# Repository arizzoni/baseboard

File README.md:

# baseboard
hardware audio effects I/O baseboard

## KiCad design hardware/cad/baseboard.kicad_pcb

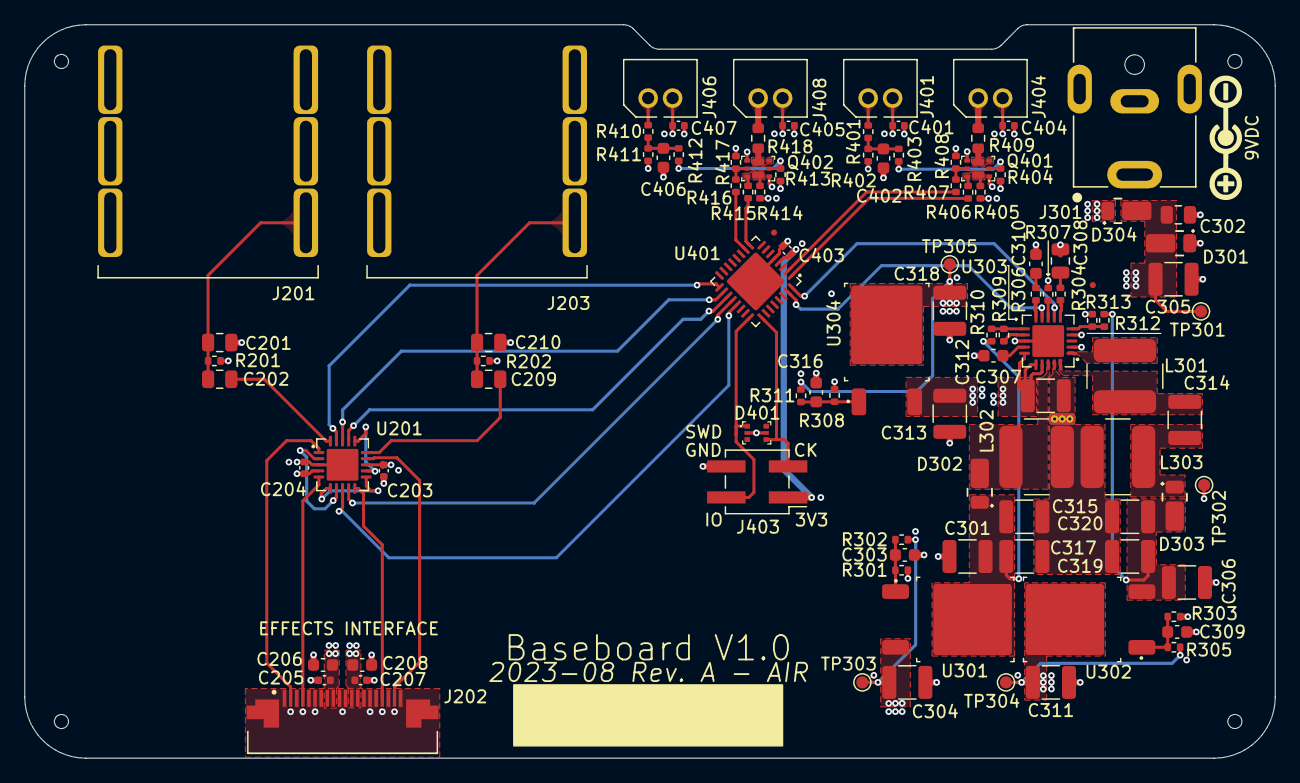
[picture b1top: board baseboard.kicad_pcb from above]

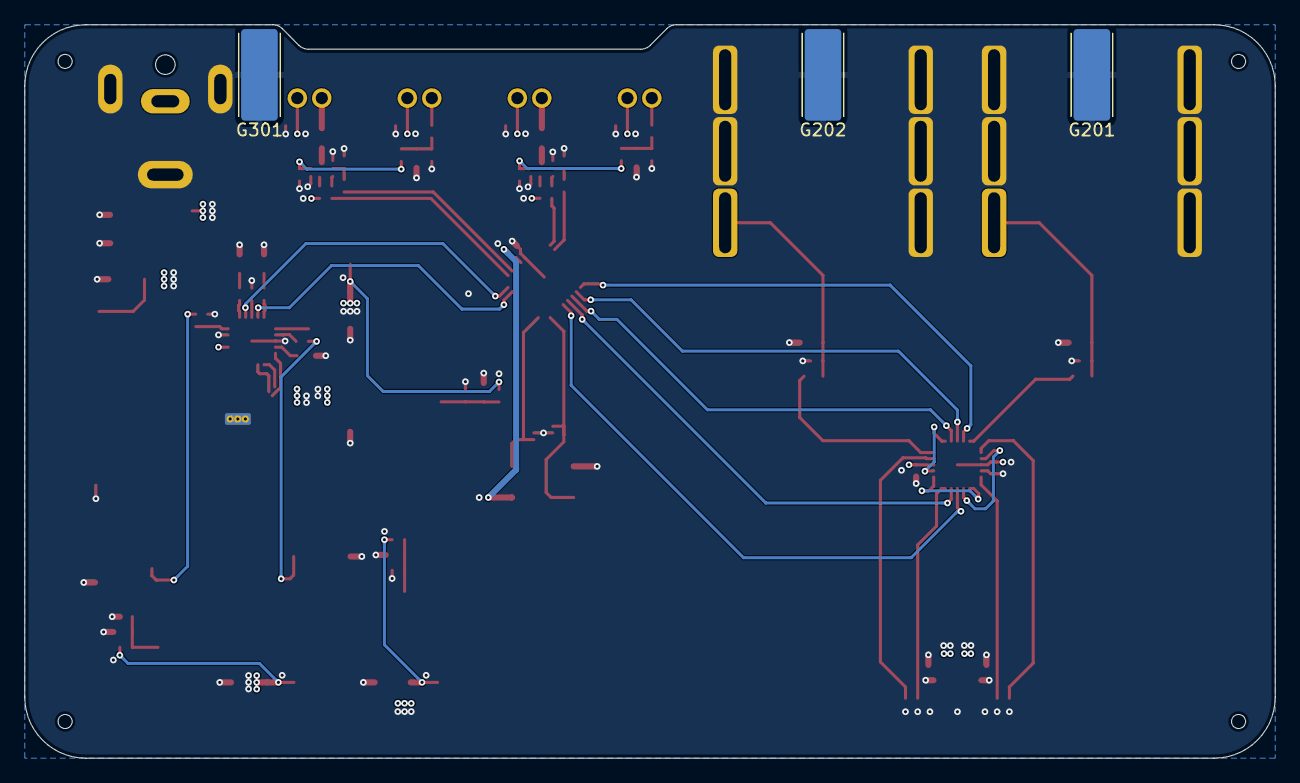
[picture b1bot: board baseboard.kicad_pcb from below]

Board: 4 copper layers, 102.3 x 60.0 mm, 110 parts (3 on the bottom side), 63 nets.

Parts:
C201, C210, C302: 150pF; C_0805_2012Metric
C202, C209: 39nF; C_0805_2012Metric
C203, C204, C205, C207, C401, C403, C404, C405, C407: 100nF; C_0402_1005Metric
C206, C208, C303, C309, C312, C316, C402, C406: 2.2μF; C_0603_1608Metric
C301, C304, C305, C306, C307, C311, C313, C314, C315, C317, C318, C319, C320: 10μF; C_1210_3225Metric
C308: 58nF; C_0805_2012Metric
C310: 10nF; C_0603_1608Metric
D301: DFLZ13Q-7; D_PowerDI-123_THERMAL_PAD
D302, D303, D304: DFLS240L-7; D_PowerDI-123_THERMAL_PAD
D401: RSB12JS2
FID301, FID401: FIDUCIAL; Fiducial_0.5mm_Mask1mm
G201, G202, G301: CHASSIS; Harwin_EMI_Finger_S7061-46R
H401, H402, H403, H404: JLC_TOOLING_HOLE; JLC_Tooling_hole
J201, J203: ACJS-IHS; Amphenol_ACJS-IHS
J202: SFV20R-2STE1HLF; AMPHENOL_SFV20R-2STE1HLF
J301: PJ-063AH; CUI_PJ-063AH
J401, J404, J406, J408: 6-440054-2; TE_HPI_2.0MM_PITCH_MALE_HEADER_2POS
J403: 2x2 PIN HEADER; PinHeader_2x02_P2.54mm_Vertical_SMD
L301, L302, L303: 22μH; L_TDK_VLS6045EX_VLS6045AF
NT301: NET TIE; Net_Tie
Q401, Q402: DMN2050; DMN2050LFDB
R201, R310, R312: 1MΩ; R_0402_1005Metric
R202, R402, R411: 49.9kΩ; R_0402_1005Metric
R301, R303, R404, R408, R413, R417: 750Ω; R_0402_1005Metric
R302, R305, R311, R401, R403, R406, R407, R410, R412, R415, R416: 120Ω; R_0402_1005Metric
R304: 33kΩ; R_0402_1005Metric
R306: 3.3kΩ; R_0402_1005Metric
R307, R313: 71.5kΩ; R_0402_1005Metric
R308, R405, R414: 200Ω; R_0402_1005Metric
R309: 62.5kΩ; R_0402_1005Metric
R409, R418: 15Ω; R_0603_1608Metric
TP301: DC_IN; TestPoint_Pad_D1.0mm
TP302: GND; TestPoint_Pad_D1.0mm
TP303: -9V; TestPoint_Pad_D1.0mm
TP304: +9V; TestPoint_Pad_D1.0mm
TP305: +3V3; TestPoint_Pad_D1.0mm
U201: ADG5434; LFCSP-20-1EP_4x4mm_P0.5mm_EP2.6x2.6mm
U301: LM337KVURG3; TO-252-2
U302, U304: LM317MDT-TR; TO-252-2
U303: ADP5070; LFCSP-20-1EP_4x4mm_P0.5mm_EP2.6x2.6mm
U401: STM32G031K8U6; QFN-32-1EP_5x5mm_P0.5mm_EP3.45x3.45mm

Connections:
+3V3: C318.2, C401.2, C403.2, C404.2, C405.2, C407.2, J401.2, J403.1, J404.2, J406.2, J408.2, R311.1, R405.1, R414.1, TP305.1, U304.2 (VO), U401.4 (VDD)
+9V: C203.1, C205.2, C206.2, C311.2, J202.8, J202.9, R305.1, TP304.1, U201.13 (VDD), U302.2 (VO)
+9V_EN: U303.7 (EN1), U401.32 (PB8)
+12V_RAW: C306.2, C319.2, C320.2, D303.1 (K), R312.2, U302.3 (VI)
-9V: C204.1, C207.2, C208.2, C304.2, J202.12, J202.13, R302.1, TP303.1, U201.3 (VSS), U201.21 (VSS), U301.3 (VO)
-9V_EN: U303.9 (EN2), U401.31 (PB7)
-12V_RAW: C301.2, C315.2, C317.2, D302.2 (A), R310.1, U301.2 (VI)
/AUDIO/AUDIO_A_TO_B: U201.6 (D2), U201.11 (D3)
/AUDIO/AUDIO_IN-: C201.1, C202.2, J201.T, R201.1
/AUDIO/AUDIO_OUT: C209.1, C210.1, J203.T, R202.1
/AUDIO/BYPASS_A: U201.2 (S1B), U201.7 (S2A)
/AUDIO/BYPASS_B: U201.12 (S3B), U201.16 (S4A)
/MICROCONTROLLER/SWDCK: D401.4, J403.3, U401.25 (PA14)
/MICROCONTROLLER/SWDIO: D401.1, J403.2, U401.24 (PA13)
/MICROCONTROLLER/VD_FTSW_A: Q402.6 (D), R414.2, R415.1
/MICROCONTROLLER/VD_FTSW_B: Q401.6 (D), R405.2, R406.1
/MICROCONTROLLER/VG_FTSW_A: Q402.2 (G), R412.2, R413.1
/MICROCONTROLLER/VG_FTSW_B: Q401.2 (G), R403.2, R404.1
/MICROCONTROLLER/VG_LEDA: Q402.5 (G), R416.2, R417.1
/MICROCONTROLLER/VG_LEDB: Q401.5 (G), R407.2, R408.1
/MICROCONTROLLER/VS_A: Q402.3 (D), R418.2
/MICROCONTROLLER/VS_B: Q401.3 (D), R409.2
/MICROCONTROLLER/V_FTSW_FILT_A: C406.2, R410.2, R411.2, R412.1
/MICROCONTROLLER/V_FTSW_FILT_B: C402.2, R401.2, R402.2, R403.1
/MICROCONTROLLER/V_FTSW_RAW_A: J406.1, R410.1
/MICROCONTROLLER/V_FTSW_RAW_B: J401.1, R401.1
/MICROCONTROLLER/V_LEDA: J408.1, R418.1
/MICROCONTROLLER/V_LEDB: J404.1, R409.1
/POWER/3V3REG_FB: C316.2, R308.1, R311.2, U304.1 (ADJ)
/POWER/+9VREG_FBP: C309.2, R303.1, R305.2, U302.1 (ADJ)
/POWER/-9VREG_FBN: C303.2, R301.1, R302.2, U301.1 (ADJ)
/POWER/DC_IN_RAW: D304.2 (A), J301.2
/POWER/VSW1A: C314.2, L301.2, U303.20 (SW1)
/POWER/VSW1B: C314.1, D303.2 (A), L303.2
/POWER/VSW1INBK: L301.1, U303.1 (INBK)
/POWER/VSW2: D302.1 (K), L302.2, U303.18 (SW2)
/POWER/VSW_COMP1: R304.2, U303.6 (COMP1)
/POWER/VSW_COMP2: R306.2, U303.10 (COMP2)
/POWER/VSW_FB1: R312.1, R313.2, U303.5 (FB1)
/POWER/VSW_FB2: R309.1, R310.2, U303.11 (FB2)
/POWER/VSW_SOFT_START: R307.2, U303.8 (SS)
/POWER/VSW_VREF: R309.2, U303.12 (VREF)
/POWER/VSW_VREG: C312.2, U303.14 (VREG)
AUDIO_IN_A: J202.2, U201.1 (D1)
AUDIO_IN_B: J202.17, U201.10 (S3A)
AUDIO_IN_FILT: C202.1, U201.20 (S1A)
AUDIO_OUT_A: J202.4, U201.5 (S2B)
AUDIO_OUT_B: J202.19, U201.14 (S4B)
AUDIO_OUT_FILT: C209.2, U201.15 (D4)
DC_IN: C302.1, C305.2, C307.2, C313.2, D301.1 (K), D304.1 (K), TP301.1, U303.2 (SYNC/FREQ), U303.15 (PVIN1), U303.16 (PVINSYS), U303.17 (PVIN2), U304.3 (VI)
FTSW_A: R415.2, U401.9 (PA2)
FTSW_B: R406.2, U401.1 (PB9)
GND: C201.2, C203.2, C204.2, C205.1, C206.1, C207.1, C208.1, C210.2, C301.1, C302.2, C303.1, C304.1, C305.1, C306.1, C308.1, C309.1, C310.1, C311.1, C312.1, C313.1, C316.1, C318.1, C401.1, C402.1, C403.1, C404.1, C405.1, C406.1, C407.1, D301.2 (A), D401.2, D401.5, G201.1, G202.1, G301.1, J201.R, J201.RN, J201.S, J201.SN, J201.TN, J202.1, J202.3, J202.5, J202.6, J202.7, J202.10, J202.11, J202.14, J202.15, J202.16, J202.18, J202.20, J202.SH1, J202.SH2, J203.R, J203.RN, J203.S, J203.SN, J203.TN, J301.1, J301.S1, J301.S2, J403.4, NT301.2, Q401.1 (S), Q401.4 (S), Q402.1 (S), Q402.4 (S), R201.2, R202.2, R301.2, R303.2, R307.1, R308.2, R313.1, R402.1, R404.2, R408.2, R411.1, R413.2, R417.2, TP302.1, U201.4 (GND), U303.4 (SLEW), U303.13 (AGND), U303.21 (AGND), U401.5 (VSS), U401.33 (VSS)
GND1: C307.1, C315.1, C317.1, C319.1, C320.1, L302.1, L303.1, NT301.1, U303.19 (PGND)
LEDA_EN: R416.1, U401.10 (PA3)
LEDB_EN: R407.1, U401.2 (PC14)
unnamed: C308.2, R304.1
unnamed: C310.2, R306.1
SW_IN1: U201.19 (IN1), U401.17 (PB2)
SW_IN2: U201.8 (IN2), U401.21 (PA10/NC)
SW_IN3: U201.9 (IN3), U401.20 (PC6)
SW_IN4: U201.17 (IN4), U401.19 (PA9/NC)
~SW_EN: U201.18 (~EN), U401.18 (PA8)

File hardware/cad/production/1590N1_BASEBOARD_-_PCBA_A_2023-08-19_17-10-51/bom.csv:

Designator,Footprint,Quantity,Value,LCSC Part #
"C201, C210, C302",0805,3,150pF,
"C202, C209",0805,2,39nF,
"C203, C204, C205, C207, C401, C403, C404, C405, C407",0402,9,100nF,
"C206, C208, C303, C309, C312, C316, C402, C406",0603,8,2.2μF,
"C301, C304, C305, C306, C307, C311, C313, C314, C315, C317, C318, C319, C320",1210,13,10μF,
C308,0805,1,58nF,
C310,0603,1,10nF,
D301,D_PowerDI-123_THERMAL_PAD,1,DFLZ13Q-7,
"D302, D303, D304",D_PowerDI-123_THERMAL_PAD,3,DFLS240L-7,
D401,RSB12JS2,1,RSB12JS2,
"FID301, FID401",Fiducial_0.5mm_Mask1mm,2,FIDUCIAL,
"G201, G202, G301",Harwin_EMI_Finger_S7061-46R,3,CHASSIS,
"H401, H402, H403, H404",JLC_Tooling_hole,4,JLC_TOOLING_HOLE,
"J201, J203",Amphenol_ACJS-IHS,2,ACJS-IHS,
J202,AMPHENOL_SFV20R-2STE1HLF,1,SFV20R-2STE1HLF,
J301,CUI_PJ-063AH,1,PJ-063AH,
"J401, J404, J406, J408",TE_HPI_2.0MM_PITCH_MALE_HEADER_2POS,4,6-440054-2,
J403,PinHeader_2x02_P2.54mm_Vertical_SMD,1,2x2 PIN HEADER,
"L301, L302, L303",L_TDK_VLS6045EX_VLS6045AF,3,22μH,
"Q401, Q402",DMN2050LFDB,2,DMN2050,
"R201, R310, R312",0402,3,1MΩ,
"R202, R402, R411",0402,3,49.9kΩ,
"R301, R303, R404, R408, R413, R417",0402,6,750Ω,
"R302, R305, R311, R401, R403, R406, R407, R410, R412, R415, R416",0402,11,120Ω,
R304,0402,1,33kΩ,
R306,0402,1,3.3kΩ,
"R307, R313",0402,2,71.5kΩ,
"R308, R405, R414",0402,3,200Ω,
R309,0402,1,62.5kΩ,
"R409, R418",0603,2,15Ω,
TP301,TestPoint_Pad_D1.0mm,1,DC_IN,
TP302,TestPoint_Pad_D1.0mm,1,GND,
TP303,TestPoint_Pad_D1.0mm,1,-9V,
TP304,TestPoint_Pad_D1.0mm,1,+9V,
TP305,TestPoint_Pad_D1.0mm,1,+3V3,
U201,LFCSP-20-1EP_4x4mm_P0.5mm_EP2.6x2.6mm,1,ADG5434,
U301,TO-252-2,1,LM337KVURG3,
"U302, U304",TO-252-2,2,LM317MDT-TR,
U303,LFCSP-20-1EP_4x4mm_P0.5mm_EP2.6x2.6mm,1,ADP5070,
U401,QFN-32-1EP_5x5mm_P0.5mm_EP3.45x3.45mm,1,STM32G031K8U6,

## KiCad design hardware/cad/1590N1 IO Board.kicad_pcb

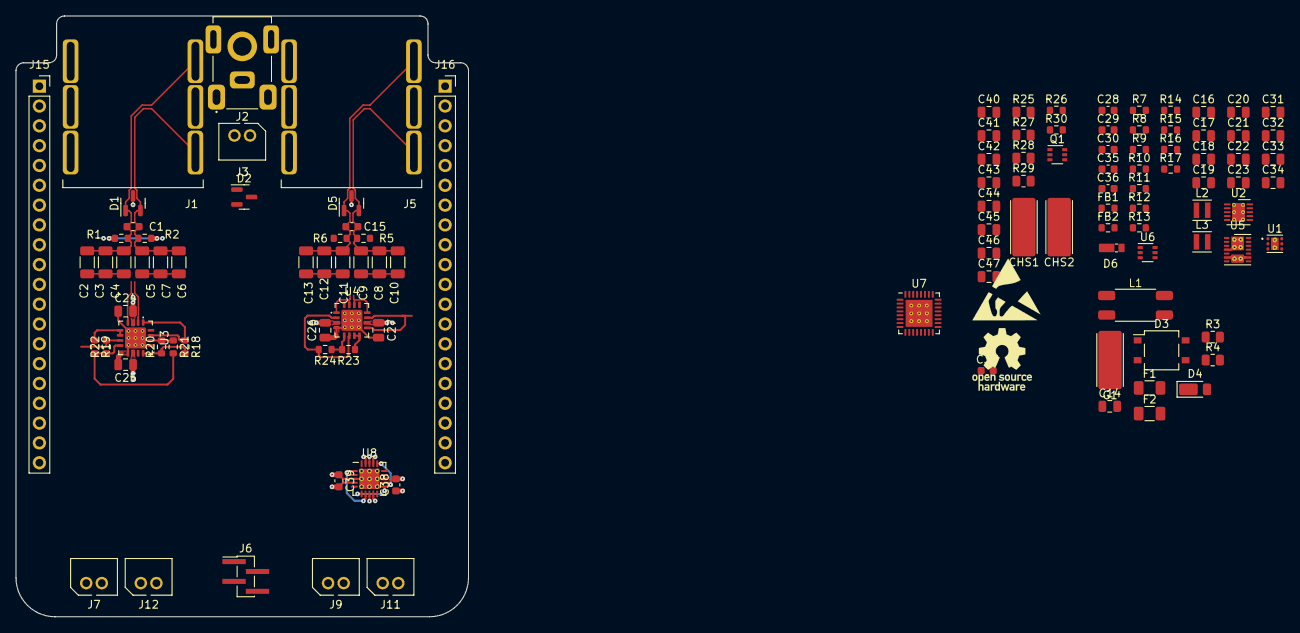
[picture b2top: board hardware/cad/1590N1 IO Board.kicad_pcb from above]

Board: 4 copper layers, 58.0 x 77.0 mm, 115 parts (0 on the bottom side), 76 nets.

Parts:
C1, C15: 6p; C_0603_1608Metric
C2, C3, C4, C5, C6, C7, C8, C9, C10, C11, C12, C13: 330n; C_1206_3216Metric
C14, C16, C17, C18, C19, C20, C21, C22, C23, C31, C32, C41, C45, C46, C47: 22u; C_0805_2012Metric
C24, C25, C26, C27, C33, C34, C40, C42, C43, C44: 100n; C_0805_2012Metric
C28, C29, C35, C36: 10n; C_0603_1608Metric
C30, C37, C38, C39: 100n; C_0603_1608Metric
CHS1, CHS2: Chassis; Harwin_EMI_Finger_S7061-46R
D1, D2, D5: PESD12VL2BT,215; SOT-23
D3: FULL BRIDGE; TO-269AA
D4: DFLZ13Q-7; D_PowerDI-123
D6: RSX051VAM30TR; SOD-323HE
F1, F2: PPTC; Fuse_1206_3216Metric
FB1, FB2: MPZ1608S102ATA00; R_0603_1608Metric
G1: Chassis; Harwin_EMI_Finger_S7061-46R
G2: Logo_Open_Hardware_Small; OSHW-Logo_7.5x8mm_SilkScreen
G3: SYM_ESD_Small; ESD-Logo_8.9x8mm_SilkScreen
J1, J5: 1/4" JACK, STEREO; Amphenol_ACJS-IHS
J2: DC POWER JACK; CUI_PJ-047
J3, J7, J9, J11, J12: 6-440054-2; TE_HPI_2.0MM_PITCH_MALE_HEADER_2POS
J6: Conn_01x04_Pin; PinHeader_1x04_P1.27mm_Vertical_SMD_Pin1Left
J15, J16: Conn_01x20_Pin; PinSocket_1x20_P2.54mm_Vertical
L1: 11u; BOURNS_DR331-113BE
L2, L3: 15u; L_Taiyo-Yuden_NR-24xx
Q1: DMN63D8LDW; SOT-363_SC-70-6
R1, R2: 1M; R_0603_1608Metric
R3, R4: 0R; R_0805_2012Metric
R5, R6, R18, R19, R20, R21, R22, R23, R24: 49.9K; R_0603_1608Metric
R7, R10, R11, R13: 62k; R_0603_1608Metric
R8, R26, R30: 10k; R_0603_1608Metric
R9, R12, R14, R17: 499k; R_0603_1608Metric
R15, R16: 78.7k; R_0603_1608Metric
R25, R27, R28, R29: 47R; R_0805_2012Metric
U1: TLV767; WSON-6-1EP_2x2mm_P0.65mm_EP1x1.6mm_ThermalVias
U2: LT3463; DFN-10-1EP_3x3mm_P0.5mm_EP1.65x2.38mm_ThermalVias
U3, U4: OPA1679
U5: LT3032; DE14MA
U6: 74LVC2G17; SOT-363_SC-70-6
U7: STM32G031K8U6TR; QFN-32-1EP_5x5mm_P0.5mm_EP3.45x3.45mm_ThermalVias
U8: ADG5434; LFCSP-20-1EP_4x4mm_P0.5mm_EP2.6x2.6mm_ThermalVias

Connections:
+3V3: C21.2, C30.2, C37.2, C40.2, C42.2, C43.2, C44.2, J6.1, J7.2, J9.1, J11.1, J12.2, R7.1, R13.1, U1.1 (OUT), U6.5 (VCC), U7.4 (VDD)
+9V: C24.2, C26.2, C28.1, C31.2, C33.2, C35.1, C38.2, C46.2, J15.19, R14.1, U3.3 (V+), U4.3 (V+), U5.1 (OUTP), U8.13 (VDD)
+9V_EN: U2.9 (~SHDN1), U5.12 (~SHDNP), U7.15 (PB0)
+Vsw: C22.2, FB1.1, U5.14 (INP)
-9V: C25.1, C27.1, C29.1, C32.1, C34.1, C36.2, C39.1, C47.2, J16.19, R17.2, U3.10 (V-), U4.10 (V-), U5.7 (OUTN), U8.3 (VSS), U8.21 (VSS)
-9V_EN: U2.8 (~SHDN2), U5.10 (~SHDNN), U7.16 (PB1)
-Vsw: C23.1, FB2.2, U5.6 (INN), U5.9 (INN), U5.16 (INN)
/Input and Output/AUDIO_IN+: C1.1, C2.1, C3.1, C4.1, D1.1 (A1), J1.S, R1.1
/Input and Output/AUDIO_IN-: C1.2, C5.1, C6.1, C7.1, D1.2 (A2), J1.T, R2.2
/Input and Output/AUDIO_OUT+: C8.1, C9.1, C10.1, C15.1, D5.2 (A2), J5.T, R5.1
/Input and Output/AUDIO_OUT-: C11.1, C12.1, C13.1, C15.2, D5.1 (A1), J5.S, R6.2
/Input and Output/BATT_SW+: J2.3, J3.1
/Input and Output/DC_IN+: D2.1 (A1), J2.2, L1.3, R4.2
/Input and Output/DC_IN-: D2.2 (A2), J2.1, L1.1, R3.2
/Input and Output/DC_IN_FUSED+: D3.1, F2.1
/Input and Output/DC_IN_FUSED-: D3.2, F1.1
/Microcontroller and Switching/AUDIO_A_TO_B: U8.6 (D2), U8.11 (D3)
/Microcontroller and Switching/BYPASS_A: U8.2 (S1B), U8.7 (S2A)
/Microcontroller and Switching/BYPASS_B: U8.12 (S3B), U8.16 (S4A)
/Microcontroller and Switching/SW_EN: U7.22 (PA11/PA9), U8.18 (~EN)
/Microcontroller and Switching/SW_IN1: U7.21 (PA10/NC), U8.19 (IN1)
/Microcontroller and Switching/SW_IN2: U7.18 (PA8), U8.8 (IN2)
/Microcontroller and Switching/SW_IN3: U7.19 (PA9/NC), U8.9 (IN3)
/Microcontroller and Switching/SW_IN4: U7.23 (PA12/PA10), U8.17 (IN4)
/Peripherals/V_FTSW_RAW_A: J7.1, R25.2
/Peripherals/V_FTSW_RAW_B: J12.1, R29.2
/Peripherals/V_LEDA: J9.2, R27.2
/Peripherals/V_LEDB: J11.2, R28.2
/Power/3V3REG_FB: R7.2, R8.1, R13.2, U1.2 (FB)
/Power/9VREG_FBN: R16.2, R17.1, U5.8 (ADJN)
/Power/9VREG_FBP: R14.2, R15.1, U5.2 (ADJP)
/Power/FB1: R9.2, R10.1, U2.10 (FB1)
/Power/FB2: R11.1, R12.1, U2.6 (FB2)
/Power/VBYPP: C28.2, U5.3 (BYPP)
/Power/VREF: R11.2, U2.7 (VREF)
/Power/VSW1: L2.1, U2.2 (SW1)
/Power/VSW2: L3.2, U2.4 (SW2)
/Power/V_SW_D2: C17.1, D6.1 (K), U2.5 (D2)
AUDIO_IN_A: J15.2, U8.20 (S1A)
AUDIO_IN_B: J15.7, U8.10 (S3A)
AUDIO_IN_FILT+: C2.2, C3.2, C4.2, U3.4 (+B)
AUDIO_IN_FILT-: C5.2, C6.2, C7.2, U3.2 (+A)
AUDIO_IN_SE: R22.2, U3.7, U8.1 (D1)
AUDIO_OUT_A: J16.2, U8.5 (S2B)
AUDIO_OUT_B: J16.7, U8.14 (S4B)
AUDIO_OUT_FILT+: C8.2, C9.2, C10.2, U4.12 (-D), U4.14
AUDIO_OUT_FILT-: C11.2, C12.2, C13.2, U4.1 (-A), U4.15
AUDIO_OUT_SE: U4.9 (+C), U4.11 (+D), U8.15 (D4)
BATT_SW-: J1.R, J3.2
DC_IN: C14.2, C16.2, C17.2, C18.2, D3.3 (+), D4.1 (K), L2.2, L3.1, U1.4 (EN), U1.6 (IN), U2.3 (VIN)
GND: C14.1, C16.1, C18.1, C19.1, C20.2, C21.1, C22.1, C23.2, C24.1, C25.2, C26.1, C27.2, C30.1, C31.1, C32.2, C33.1, C34.2, C35.2, C36.1, C37.1, C38.1, C39.2, C40.1, C41.1, C42.1, C43.1, C44.1, C45.1, C46.1, C47.1, CHS1.1 (PWR), CHS2.1 (PWR), D1.3 (common), D2.3 (common), D3.4 (-), D4.2 (A), D5.3 (common), G1.1 (PWR), J1.RN, J1.SN, J1.TN, J2.MP (MountPin), J5.R, J5.RN, J5.SN, J5.TN, J6.4, J15.1, J15.3, J15.6, J15.8, J15.20, J16.1, J16.3, J16.6, J16.8, J16.20, Q1.1 (S), Q1.4 (S), R8.2, R10.2, R15.2, R16.1, R26.2, R30.2, U1.3 (GND), U1.5 (GND), U1.7 (PAD), U2.11 (GND), U3.9 (+C), U3.11 (+D), U3.17 (GND), U4.4 (+B), U4.17 (GND), U5.4 (GND), U5.5 (GND), U5.15 (GND), U6.2 (GND), U7.5 (VSS), U7.33 (VSS), U8.4 (GND)
unnamed: C41.2, R25.1, R26.1, U6.1
unnamed: C45.2, R29.1, R30.1, U6.3
unnamed: C20.1, D6.2 (A), FB2.1, R12.2
unnamed: F1.2, L1.2, R3.1
unnamed: F2.2, L1.4, R4.1
unnamed: Q1.6 (D), R27.1
unnamed: Q1.3 (D), R28.1
unnamed: R1.2, R2.1
unnamed: R5.2, R6.1
unnamed: R20.2, R21.1, U3.14
unnamed: C19.2, FB1.2, R9.1, U2.1 (VOUT1)
unnamed: R18.1, U3.1 (-A), U3.15
unnamed: R19.1, U3.5 (-B), U3.6
unnamed: R19.2, R21.2, R22.1, U3.8 (-C)
unnamed: R18.2, R20.1, U3.12 (-D)
unnamed: R24.2, U4.2 (+A), U4.6
unnamed: R23.2, R24.1, U4.5 (-B)
unnamed: R23.1, U4.7, U4.8 (-C)
unnamed: C29.2, U5.11 (BYPN)
SWDCK: J6.3, U7.25 (PA14)
SWDIO: J6.2, U7.24 (PA13)
VLED1: Q1.2 (G), U7.28 (PB4)
VLED2: Q1.5 (G), U7.27 (PB3)
V_FTSW_A: U6.6, U7.2 (PC14)
V_FTSW_B: U6.4, U7.3 (PC15)

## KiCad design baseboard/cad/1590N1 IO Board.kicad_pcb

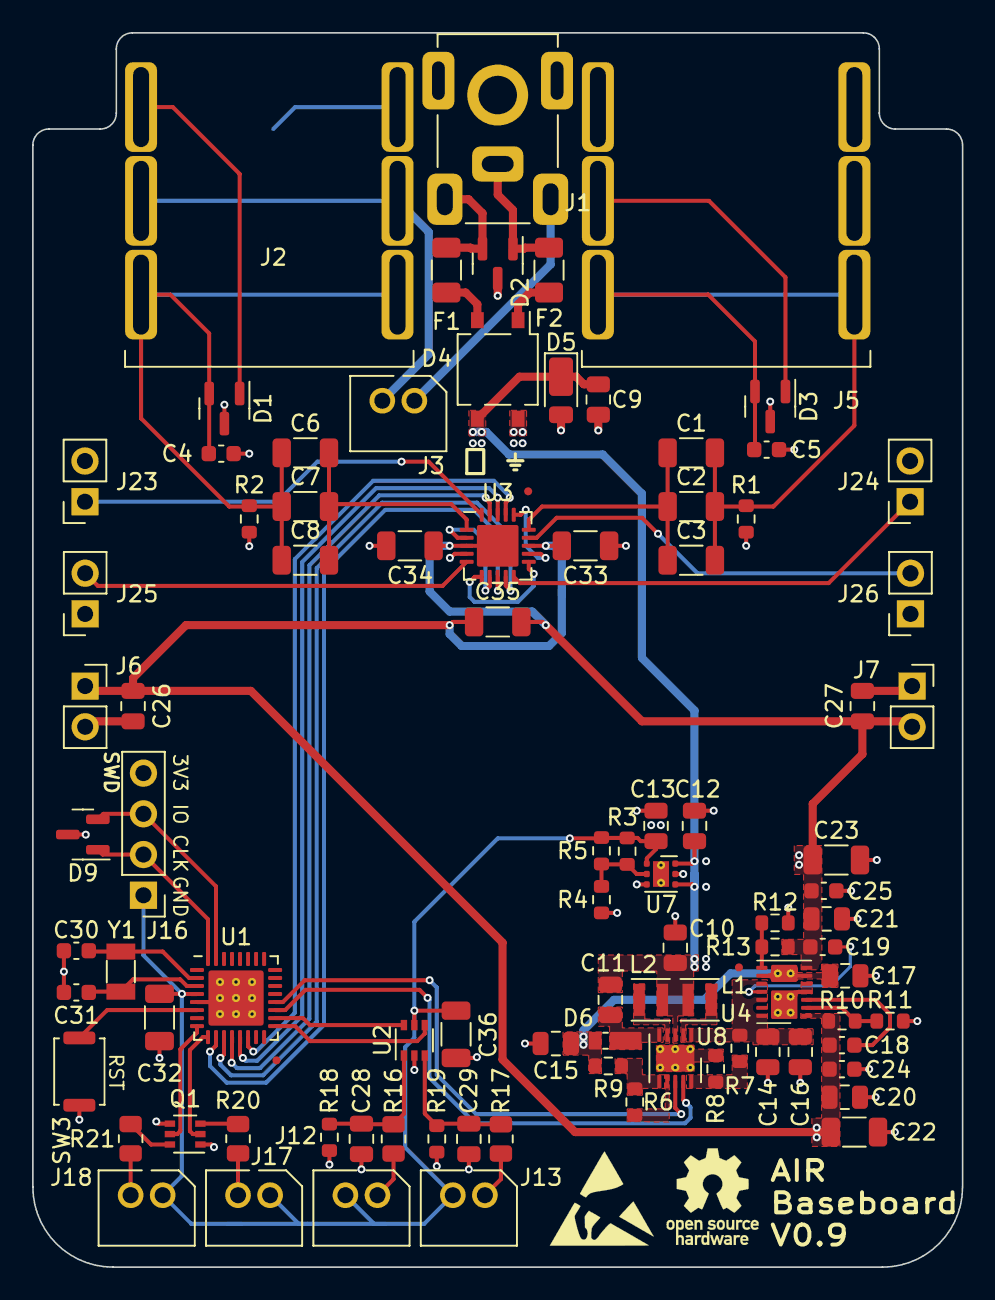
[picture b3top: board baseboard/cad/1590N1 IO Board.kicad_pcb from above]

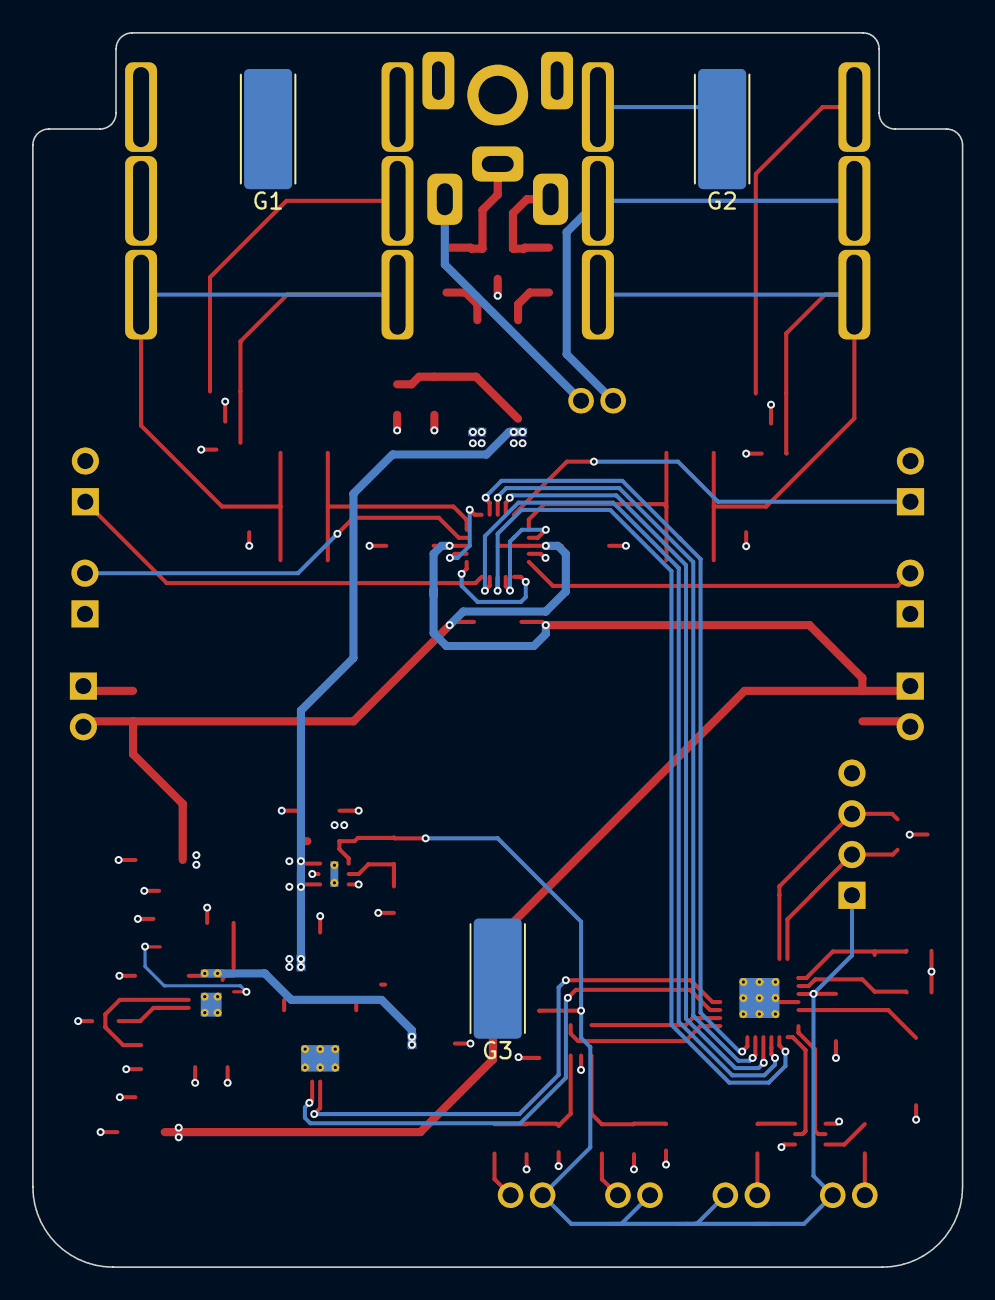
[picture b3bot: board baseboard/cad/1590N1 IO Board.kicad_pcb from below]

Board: 4 copper layers, 58.0 x 77.0 mm, 96 parts (3 on the bottom side), 59 nets.

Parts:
C1, C2, C3, C6, C7, C8: 330nF; C_1206_3216Metric
C4, C5, C30, C31: 6pF; C_0603_1608Metric
C9, C10, C11, C12, C13, C14, C15, C16, C17, C20, C21, C26, C27, C28, C29: 22μF; C_0805_2012Metric
C18, C19, C24, C25: 10nF; C_0603_1608Metric
C22, C23, C32, C33, C34, C35, C36: 100nF; C_1206_3216Metric
D1, D2, D3, D9: PESD12VL2BT,215; SOT-23
D4: FULL BRIDGE; TO-269AA
D5: DFLZ13Q-7; D_PowerDI-123
D6: RSX051VAM30TR; SOD-323HE
F1, F2: PPTC; Fuse_1206_3216Metric
FID1, FID2, FID3: Fiducial; Fiducial_0.5mm_Mask1mm
G1, G2, G3: Chassis; Harwin_EMI_Finger_S7061-46R
J1: DC POWER JACK; CUI_PJ-047
J2, J5: 1/4" JACK, STEREO; Amphenol_ACJS-IHS
J3, J12, J13, J17, J18: 6-440054-2; TE_HPI_2.0MM_PITCH_MALE_HEADER_2POS
J6, J7, J23, J24, J25, J26: 2P_HEADER; PinSocket_1x02_P2.54mm_Vertical
J16: Conn_01x04_Pin; PinHeader_1x04_P2.54mm_Vertical
L1, L2: 15μH; L_Taiyo-Yuden_NR-24xx
Q1: Q_Dual_NMOS_S1G1D2S2G2D1; SOT-363_SC-70-6
R1: 49.9kΩ; R_0603_1608Metric
R2: 1MΩ; R_0603_1608Metric
R3, R5, R6, R8: 62kΩ; R_0603_1608Metric
R4, R18, R19: 10kΩ; R_0603_1608Metric
R7, R9, R10, R13: 499kΩ; R_0603_1608Metric
R11, R12: 78.7kΩ; R_0603_1608Metric
R16, R17, R20, R21: 47Ω; R_0805_2012Metric
SW3: SW_DIP_x01; SW_Push_SPST_NO_Alps_SKRK
U1: STM32G031K8Ux; QFN-32-1EP_5x5mm_P0.5mm_EP3.45x3.45mm_ThermalVias
U2: 74LVC2G17; SOT-363_SC-70-6
U3: ADG5434; LFCSP-20-1EP_4x4mm_P0.5mm_EP2.6x2.6mm
U4: LT3032; DE14MA
U7: TLV767; WSON-6-1EP_2x2mm_P0.65mm_EP1x1.6mm_ThermalVias
U8: LT3463; DFN-10-1EP_3x3mm_P0.5mm_EP1.65x2.38mm_ThermalVias
Y1: 830054236; Crystal_SMD_3215-2Pin_3.2x1.5mm

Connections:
+3V3: C13.2, C32.2, C36.2, J12.2, J13.2, J16.1, J17.1, J18.1, R3.1, R5.1, U1.4 (VDD), U2.5 (VCC), U7.1 (OUT)
+9V: C18.1, C20.2, C22.2, C24.1, C26.2, C33.2, C35.2, J6.1, R10.1, U3.13 (VDD), U4.1 (OUTP)
+12V_EN: U1.19 (PA9/NC), U8.9 (~SHDN1)
+Vsw: C14.2, C16.2, R7.1, U4.10 (~SHDNN), U4.12 (~SHDNP), U4.14 (INP), U8.1 (VOUT1)
-9V: C19.1, C21.1, C23.1, C25.2, C27.2, C34.1, C35.1, J7.2, R13.2, U3.3 (VSS), U3.21 (VSS), U4.7 (OUTN)
-12V_EN: U1.20 (PC6), U8.8 (~SHDN2)
-Vsw: C15.1, C17.1, D6.2 (A), R9.2, U4.6 (INN), U4.9 (INN), U4.16 (INN)
/Input and Output/AUDIO_IN: C4.2, C6.1, C7.1, C8.1, D1.2 (A2), J2.T, J2.TN, R2.1
/Input and Output/AUDIO_OUT: C1.2, C2.2, C3.2, C5.1, D3.2 (A2), J5.T, J5.TN, R1.2
/Input and Output/BATT_SW_A: J1.3, J3.1
/Input and Output/BATT_SW_B: J2.R, J2.RN, J3.2
/Input and Output/DC_IN+: D2.1 (A1), F2.2, J1.2
/Input and Output/DC_IN-: D2.2 (A2), F1.2, J1.1
/Input and Output/DC_IN_FUSED+: D4.1, F2.1
/Input and Output/DC_IN_FUSED-: D4.2, F1.1
/Microcontroller and Switching/AUDIO_A_TO_B: U3.6 (D2), U3.11 (D3)
/Microcontroller and Switching/BYPASS_A: U3.2 (S1B), U3.7 (S2A)
/Microcontroller and Switching/BYPASS_B: U3.12 (S3B), U3.16 (S4A)
/Microcontroller and Switching/XO1: C30.1, U1.2 (PC14), Y1.1
/Microcontroller and Switching/XO2: C31.1, U1.3 (PC15), Y1.2
/Peripherals/V_FTSW_RAW_A: J12.1, R16.2
/Peripherals/V_FTSW_RAW_B: J13.1, R17.2
/Peripherals/V_LEDA: J18.2, R21.2
/Peripherals/V_LEDB: J17.2, R20.2
/Power/5VREG_FB: R3.2, R4.1, R5.2, U7.2 (FB)
/Power/+9VREG_FBP: R10.2, R11.1, U4.2 (ADJP)
/Power/-9VREG_FBN: R12.2, R13.1, U4.8 (ADJN)
/Power/FB1: R7.2, R8.1, U8.10 (FB1)
/Power/FB2: R6.2, R9.1, U8.6 (FB2)
/Power/VBYPN: C19.2, U4.11 (BYPN)
/Power/VBYPP: C18.2, U4.3 (BYPP)
/Power/VSW1: L1.1, U8.2 (SW1)
/Power/VSW2: L2.2, U8.4 (SW2)
/Power/V_SW_D2: C11.1, D6.1 (K), U8.5 (D2)
AUDIO_IN_A: J23.1, U3.20 (S1A)
AUDIO_IN_B: J24.1, U3.10 (S3A)
AUDIO_IN_FILT: C6.2, C7.2, C8.2, U3.1 (D1)
AUDIO_OUT_A: J25.2, U3.5 (S2B)
AUDIO_OUT_B: J26.2, U3.14 (S4B)
AUDIO_OUT_FILT: C1.1, C2.1, C3.1, U3.15 (D4)
DC_IN: C9.2, C10.2, C11.2, C12.2, D4.3 (+), D5.1 (K), L1.2, L2.1, U7.4 (EN), U7.6 (IN), U8.3 (VIN)
GND: C4.1, C5.2, C9.1, C10.1, C12.1, C13.1, C14.1, C15.2, C16.1, C17.2, C20.1, C21.2, C22.1, C23.2, C24.2, C25.1, C26.1, C27.1, C28.1, C29.1, C30.2, C31.2, C32.1, C33.1, C34.2, C36.1, D1.1 (A1), D1.3 (common), D2.3 (common), D3.1 (A1), D3.3 (common), D4.4 (-), D5.2 (A), D9.3 (common), G1.1 (GNDPWR), G2.1 (GNDPWR), G3.1 (GNDPWR), J1.MP (MountPin), J2.S, J2.SN, J5.R, J5.RN, J5.S, J5.SN, J6.2, J7.1, J16.4, J23.2, J24.2, J25.1, J26.1, Q1.1 (S), Q1.4 (S), R1.1, R2.2, R4.2, R8.2, R11.2, R12.1, R18.2, R19.2, SW3.1, U1.5 (VSS), U1.33 (VSS), U2.2 (GND), U3.4 (GND), U4.4 (GND), U4.5 (GND), U4.15 (GND), U7.3 (GND), U7.5 (GND), U7.7 (PAD), U8.11 (GND)
unnamed: C28.2, R16.1, R18.1, U2.1
unnamed: C29.2, R17.1, R19.1, U2.3
unnamed: Q1.6 (D), R21.1
unnamed: Q1.3 (D), R20.1
unnamed: U1.10 (PA3), U3.8 (IN2)
unnamed: U1.11 (PA4), U3.9 (IN3)
unnamed: U1.12 (PA5), U3.19 (IN1)
unnamed: U1.13 (PA6), U3.18 (~EN)
unnamed: U1.14 (PA7), U3.17 (IN4)
unnamed: R6.1, U8.7 (VREF)
RST: SW3.2, U1.6 (PF2)
SWDCK: D9.2 (A2), J16.3, U1.31 (PB7)
SWDIO: D9.1 (A1), J16.2, U1.32 (PB8)
VLED1: Q1.2 (G), U1.9 (PA2)
VLED2: Q1.5 (G), U1.8 (PA1)
V_FTSW_A: U1.18 (PA8), U2.6
V_FTSW_B: U1.17 (PB2), U2.4

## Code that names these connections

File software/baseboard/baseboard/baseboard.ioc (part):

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Mcu.Name=STM32G031K(4-6-8)Ux
Mcu.Package=UFQFPN32
Mcu.UserName=STM32G031K8Ux
PA10.Signal=GPIO_Output
PA11\ [PA9].Mode=I2C
PA11\ [PA9].Signal=I2C2_SCL
PA12\ [PA10].Mode=I2C
PA12\ [PA10].Signal=I2C2_SDA
PA13.Mode=Serial_Wire
PA13.Signal=SYS_SWDIO
PA14-BOOT0.Mode=Serial_Wire
PA14-BOOT0.Signal=SYS_SWCLK
PA2.Signal=GPXTI2
PA3.Signal=GPIO_Output
PA8.Signal=GPIO_Output
PA9.Signal=GPIO_Output
PB2.Signal=GPIO_Output
PB7.Signal=GPIO_Output
PB8.Signal=GPIO_Output
PB9.Signal=GPXTI9
PC14-OSC32_IN\ (PC14).Signal=GPIO_Output
PC6.Signal=GPIO_Output
PF2\ -\ NRST.Mode=Clock-out
PF2\ -\ NRST.Signal=RCC_MCO
RCC.HSE_VALUE=8000000
RCC.SYSCLKFreq_VALUE=8000000
RCC.SYSCLKSource=RCC_SYSCLKSOURCE_PLLCLK
board=custom

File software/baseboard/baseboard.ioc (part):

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Mcu.Name=STM32G031K(4-6-8)Ux
Mcu.Package=UFQFPN32
Mcu.UserName=STM32G031K8Ux
PA0.Signal=GPIO_Output
PA1.Signal=GPIO_Output
PA10.Signal=GPIO_Output
PA11\ [PA9].Signal=GPIO_Output
PA12\ [PA10].Signal=GPIO_Output
PA13.Mode=Serial_Wire
PA13.Signal=SYS_SWDIO
PA14-BOOT0.Mode=Serial_Wire
PA14-BOOT0.Signal=SYS_SWCLK
PA8.Signal=GPIO_Output
PA9.Signal=GPIO_Output
PB0.Signal=GPIO_Output
PB1.Signal=GPIO_Output
PC14-OSC32_IN\ (PC14).Signal=GPXTI14
PC15-OSC32_OUT\ (PC15).Signal=GPXTI15
RCC.HSE_VALUE=12000000
RCC.SYSCLKFreq_VALUE=8000000
RCC.SYSCLKSource=RCC_SYSCLKSOURCE_PLLCLK
board=custom

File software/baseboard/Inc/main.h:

/* USER CODE BEGIN Header */
/**
  ******************************************************************************
  * @file           : main.h
  * @brief          : Header for main.c file.
  *                   This file contains the common defines of the application.
  ******************************************************************************
  * @attention
  *
  * Copyright (c) 2023 STMicroelectronics.
  * All rights reserved.
  *
  * This software is licensed under terms that can be found in the LICENSE file
  * in the root directory of this software component.
  * If no LICENSE file comes with this software, it is provided AS-IS.
  *
  ******************************************************************************
  */
/* USER CODE END Header */

/* Define to prevent recursive inclusion -------------------------------------*/
#ifndef __MAIN_H
#define __MAIN_H

#ifdef __cplusplus
extern "C" {
#endif

/* Includes ------------------------------------------------------------------*/
#include "stm32l0xx_hal.h"

/* Private includes ----------------------------------------------------------*/
/* USER CODE BEGIN Includes */

/* USER CODE END Includes */

/* Exported types ------------------------------------------------------------*/
/* USER CODE BEGIN ET */

/* USER CODE END ET */

/* Exported constants --------------------------------------------------------*/
/* USER CODE BEGIN EC */

/* USER CODE END EC */

/* Exported macro ------------------------------------------------------------*/
/* USER CODE BEGIN EM */

/* USER CODE END EM */

/* Exported functions prototypes ---------------------------------------------*/
void Error_Handler(void);

/* USER CODE BEGIN EFP */

/* USER CODE END EFP */

/* Private defines -----------------------------------------------------------*/
#define VDDA__EN_Pin GPIO_PIN_14
#define VDDA__EN_GPIO_Port GPIOC
#define VDDA__ENC15_Pin GPIO_PIN_15
#define VDDA__ENC15_GPIO_Port GPIOC
#define SW_EN_Pin GPIO_PIN_1
#define SW_EN_GPIO_Port GPIOA
#define SW_IN1_Pin GPIO_PIN_4
#define SW_IN1_GPIO_Port GPIOA
#define SW_IN2_Pin GPIO_PIN_5
#define SW_IN2_GPIO_Port GPIOA
#define SW_IN3_Pin GPIO_PIN_6
#define SW_IN3_GPIO_Port GPIOA
#define SW_IN4_Pin GPIO_PIN_7
#define SW_IN4_GPIO_Port GPIOA
#define LED2_Pin GPIO_PIN_9
#define LED2_GPIO_Port GPIOA
#define LED1_Pin GPIO_PIN_10
#define LED1_GPIO_Port GPIOA
#define SWDIO_Pin GPIO_PIN_13
#define SWDIO_GPIO_Port GPIOA
#define SWDCK_Pin GPIO_PIN_14
#define SWDCK_GPIO_Port GPIOA
#define FTSW2_Pin GPIO_PIN_6
#define FTSW2_GPIO_Port GPIOB
#define FTSW1_Pin GPIO_PIN_7
#define FTSW1_GPIO_Port GPIOB

/* USER CODE BEGIN Private defines */

/* USER CODE END Private defines */

#ifdef __cplusplus
}
#endif

#endif /* __MAIN_H */

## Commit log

2023-05-06 uploaded project files
    initial commit
2023-05-06 Create LICENSE
2023-05-09 added microcontroller enable to analog power rails
2023-05-10 added reset button to microcontroller
2023-05-11 swapped micro and started layout
2023-05-11 picked a third micro for extra pins, updated drd and refdoc.mplstyle
2023-05-11 placed components and finished new micro hw
2023-05-13 swapped relays for nice analog switch, saved $4
2023-05-13 updated schematic page setup
2023-05-13 more schematic cleanup
2023-05-13 restarted layout
2023-05-18 more early layout work
2023-05-19 finished initial layout
2023-05-19 drawing sheet updates and general prep for fab
2023-05-21 cleaning up layout, added graphic symbols
2023-05-22 more layout cleanup, reorganized file directories
2023-05-23 cleaned up redundant files
2023-05-24 more layout cleanup
2023-06-01 added differential inputs and started new layout
2023-06-02 more layout updates
2023-07-21 reorganized project
2023-07-24 finalized schematic
2023-07-31 board layout first pass
2023-08-23 an inappropriately large commit
2023-08-25 updated .step file to newest model
2023-09-01 released schematic
2023-09-21 final tweaks pt. 1
2023-10-15 finalization before first board spin
2024-02-11 cleaned up old software dir
2024-02-11 started documentation
2024-02-27 got documentation template and build working
2024-02-27 minor changes before moving to new power supply topology
2024-03-05 starting to set up docs to use new latex class
2024-03-05 set up documentation
2024-03-29 started modeling circuits
2024-04-17 cleanup
2024-08-02 gigacommit
2024-08-06 lsp setup tests and monte carlo improvements
2024-08-06 set up gitignore
